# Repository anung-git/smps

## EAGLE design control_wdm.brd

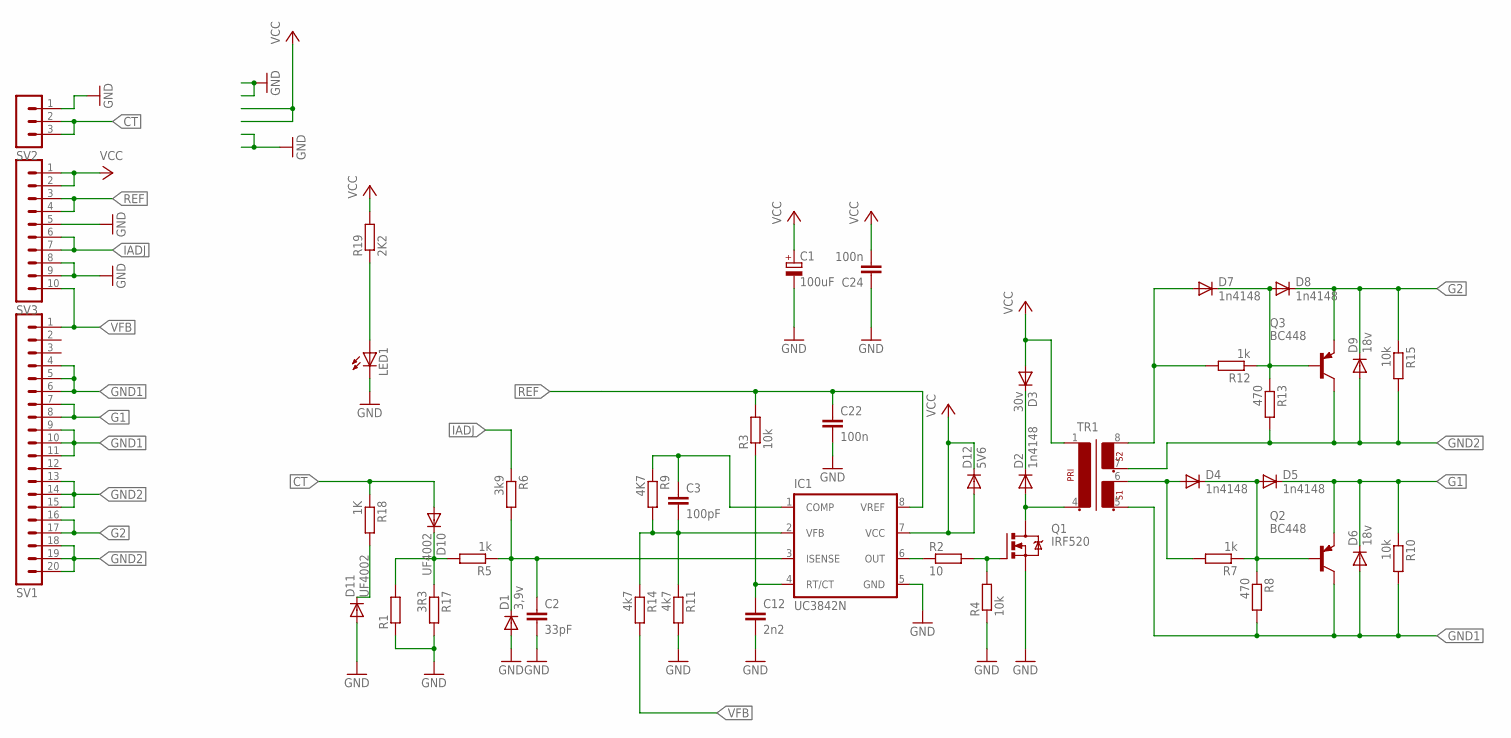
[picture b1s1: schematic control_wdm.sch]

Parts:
C1: 100uF; E5-6
C2: 33pF; C050-025X075
C3: 100pF; C050-025X075
C12: 2n2; C050-025X075
C22, C24: 100n; C050-025X075
D1: 3,9v; DO35-10
D2, D4, D5, D7, D8: 1n4148; DO35-10
D3: 30v; DO35-10
D6, D9: 18v; DO35-10
D10, D11: UF4002; DO35-10
D12: 5V6; DO35-10
IC1: UC3842N; DIL08
LED1: LED5MM
Q1: IRF520; TO220BV
Q2, Q3: BC448; TO92-EBC
R1: R-EU_0411/12; 0411/12
R2: 10; 0207/10
R3, R4, R10, R15: 10k; 0207/10
R5, R7, R12: 1k; 0207/10
R6: 3k9; 0207/10
R8, R13: 470; 0207/10
R9: 4K7; 0207/10
R11, R14: 4k7; 0207/10
R17: 3R3; 0207/10
R18: 1K; 0207/10
R19: 2K2; 0207/10
SV1: MA20-1
SV2: MA03-1
SV3: MA10-1
TR1: EE20-2

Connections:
CT: D10.A, R18.1, SV2.2, SV2.3
G1: D5.C, D6.C, Q2.E, R10.1, SV1.7, SV1.8
G2: D8.C, D9.C, Q3.E, R15.1, SV1.16, SV1.17
GND: C1.-, C2.2, C12.2, C22.2, C24.1, D1.A, D11.A, IC1.5 (GND), LED1.K (C), Q1.S, R1.1, R4.1, R11.2, R17.2, SV2.1, SV3.5, SV3.8, SV3.9
GND1: D6.A, Q2.C, R8.2, R10.2, SV1.4, SV1.5, SV1.6, SV1.9, SV1.10, SV1.11, TR1.5 (3)
GND2: D9.A, Q3.C, R13.2, R15.2, SV1.13, SV1.14, SV1.15, SV1.18, SV1.19, SV1.20, TR1.7 (5)
IADJ: R6.1, SV3.6, SV3.7
unnamed: C12.1, IC1.4 (RT/CT), R3.1
unnamed: IC1.6 (OUT), R2.1
unnamed: Q1.G, R2.2, R4.2
unnamed: C2.1, D1.C, IC1.3 (ISENSE), R5.1, R6.2
unnamed: D2.A, Q1.D, TR1.4 (2)
unnamed: D2.C, D3.C
unnamed: LED1.A, R19.1
unnamed: C3.1, IC1.1 (COMP), R9.1
unnamed: D4.C, D5.A, Q2.B, R7.1, R8.1
unnamed: D4.A, R7.2, TR1.6 (4)
unnamed: D11.C, R18.2
unnamed: C3.2, IC1.2 (VFB), R9.2, R11.1, R14.1
unnamed: D7.C, D8.A, Q3.B, R12.1, R13.1
unnamed: D7.A, R12.2, TR1.8 (6)
unnamed: D10.C, R1.2, R5.2, R17.1
REF: C22.1, IC1.8 (VREF), R3.2, SV3.3, SV3.4
VCC: C1.+, C24.2, D3.A, D12.A, D12.C, IC1.7 (VCC), R19.2, SV3.1, SV3.2, TR1.1
VFB: R14.2, SV1.1, SV3.10

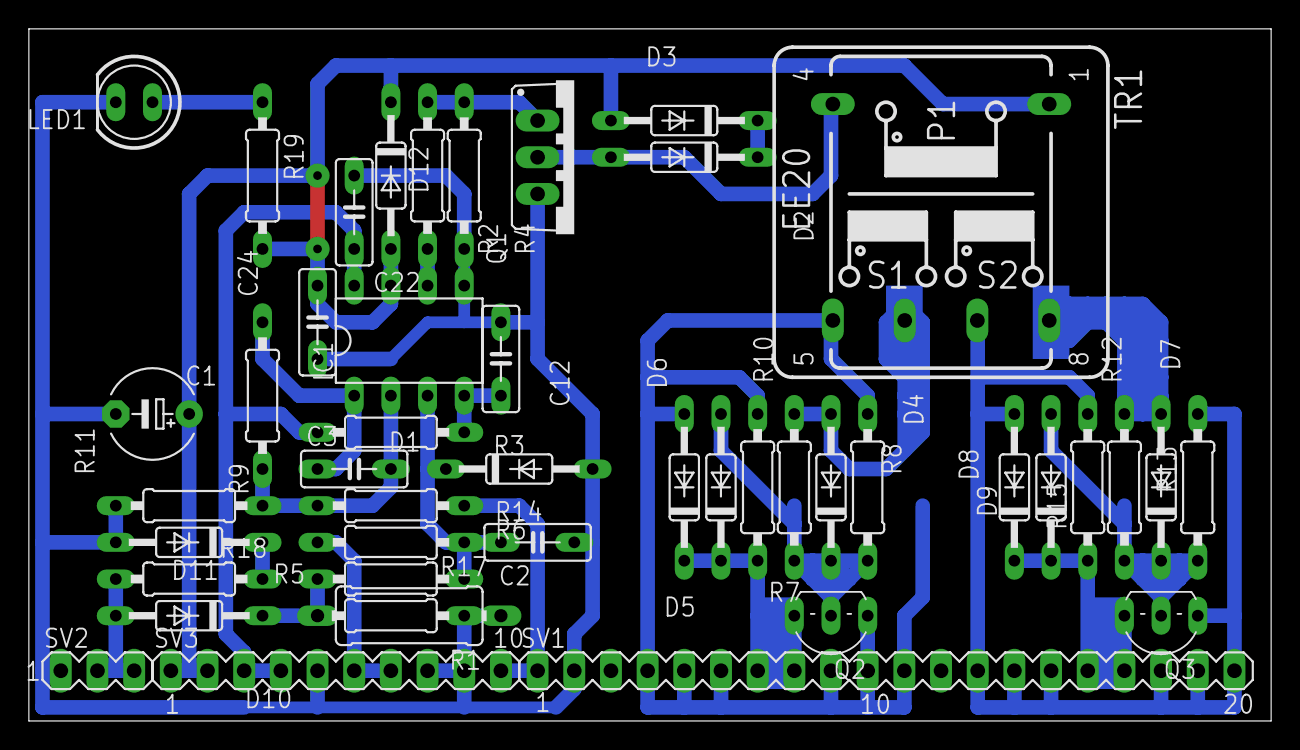
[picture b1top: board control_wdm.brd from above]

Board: 2 copper layers, 86.0 x 47.9 mm, 45 parts (0 on the bottom side), 25 nets.

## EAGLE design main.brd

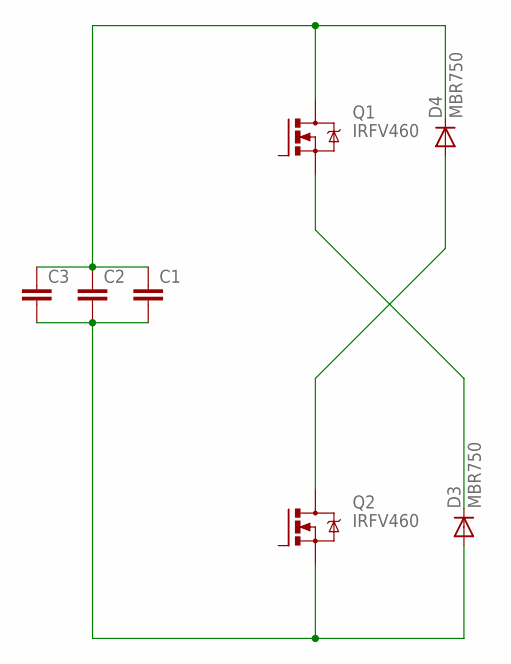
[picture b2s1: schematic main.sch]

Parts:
C1, C2, C3: C-EU375-203X418; C375-203X418
D3, D4: MBR750; TO220AC
Q1, Q2: IRFV460; TO258AA

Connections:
unnamed: D3.C, Q1.2-S (S)
unnamed: D4.A, Q2.1-D (D)
unnamed: C1.2, C2.2, C3.2, D3.A, Q2.2-S (S)
unnamed: C1.1, C2.1, C3.1, D4.C, Q1.1-D (D)

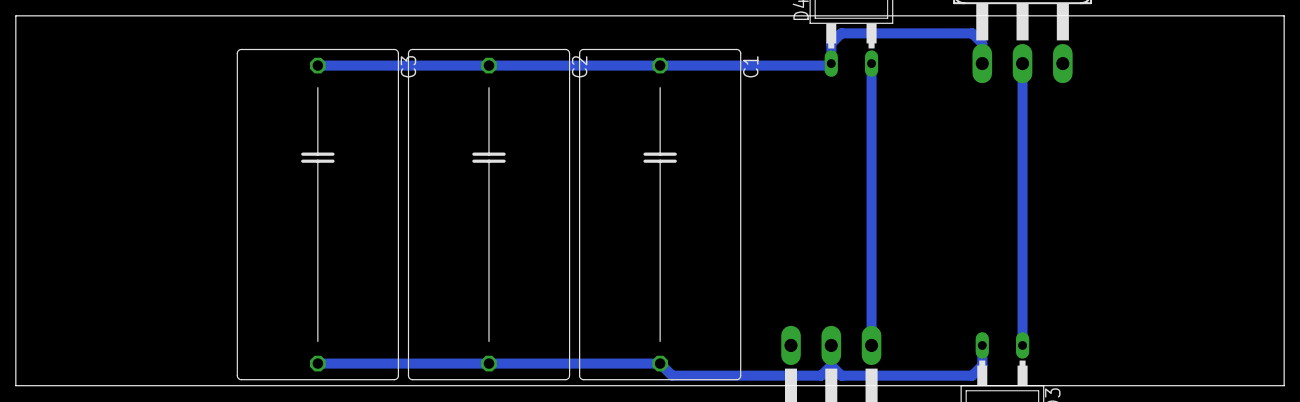
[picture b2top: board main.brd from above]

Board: 2 copper layers, 160.0 x 46.7 mm, 7 parts (0 on the bottom side), 4 nets.

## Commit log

2020-11-15 upload
